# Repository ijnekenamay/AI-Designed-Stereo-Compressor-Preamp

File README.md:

# せいせいAIにたすけてもらいながらさいきょうの Stereo Compressor / Preampをつくる

> 本書は、生成AIを使用して書いたV2164（SSI2164）を用いたステレオ・コンプレッサ／プリアンプの**詳細仕様書**である。
> 今のところ日本語のみで進めています。
> プロフェッショナル機材相当の機能と音質を実現する。

[VCA IC購入先](https://ears-modular.com/products/sound-semiconductor-fatkeys%E2%84%A2-ssi2164-vca)

---

# SSI2164 VCA コンプレッサー 製作仕様書

## 1. 全体構成図（オーディオ・パス）

本機はステレオ構成の VCA コンプレッサーであり、各ブロックは以下の順序で信号処理を行う。最終出力は正相（In-Phase）とする。
当面の目標はkiCADによるデータ作成と基板発注。基板は両面ベタグラウンドを想定しており、以下の回路設計に関してもそれを想定するものとする。

Input Buffer  
→ V/I Converter  
→ VCA Core（SSI2164）  
→ I/V Converter  
→ Make-up Gain  
→ Blend（Parallel Mix）  
→ Output Buffer  

## 2. メイン基板：オーディオ・パス詳細
- A. 入力および VCA コア部
- B. 出力およびゲイン
- C. Blend（Parallel Mix）回路
## 3. サイドチェイン・ユニット（制御部）
本機は **フィードフォワード方式**のサイドチェインを採用する。  
入力信号のレベルを検波・整流し、生成された制御電圧（CV）によってSSI2164のゲインを制御する。
※本仕様は **ステレオ構成**を前提とする。 ステレオ化は、L/R 信号を合成したCVを共通でVCAに供給する「ステレオリンク方式」とする。
- A. 検波部（Precision Rectifier）
- B. Threshold（スレッショルド）設定
- C. Ratio（圧縮率）制御
- D. Attack / Release（時定数回路）
- E. CV 出力および VCA 駆動
## 4. 全体信号フロー（俯瞰）
```text
[ INPUT L/R ]
             │
             ▼
      [[ Input Buffer ]] (OPA1644等) ───┐
             │                          │
             ├─ (A) [Buffered Bypass] ──┼──────────────────────┐
             │    (4PDT Switch: DRY)    │                      │
             │                          │                      │
             ├─ (B) [SC Pick-up]        │                      │
             │       │                  │                      │
             │       ▼                  │                      │
             │  [ SC-HPF SW ] <Deep Punch>                     │
             │       │                  │                      │
             │       ▼                  │                      │
             │  [[ Sidechain Section ]] │                      │
             │   (Summing/Rect/A/R)     │                      │
             │       │                  │                      │
             │       ▼                  │                      │
             │  [[ Stereo Link / CV ]] ─┼─── [ GR METER ]      │
             │   (CV Buffer + Trim)     │                      │
             │       │                  │                      │
             ▼       │                  │                      │
      [[ V/I Conv (R_in) ]]             │                      │
             │       │ (Gain Control)   │                      │
             ▼       ▼                  │                      │
      [[ SSI2164 VCA Core ]]            │                      │
             │                          │                      │
             ▼                          │                      │
      [[ I/V Conv / Make-up ]]          │                      │
             │                          │                      │
             ▼                          │                      │
      [[ Blend Pot ]] <WET 100%> ◄──────┘                      │
             │        (Parallel Compression)                   │
             ▼                                                 │
      [[ Output Buffer ]] (OPA1644等)                          │
             │                                                 │
             ├─ [ Saturation SW ] <Warmth & Punch>             │
             │                                                 │
             ▼                                                 │
      [ 4PDT Switch ] (WET / DRY 切り替え) ◄────────────────────┘
             │
             ▼
       [ OUTPUT L/R ]

```

## 5. オーディオ・パス回路図
### Input BufferとV/I Converter（SSI2164入力）

- 構成：ボルテージフォロワ
- 出力は
  - VCA用
  - サイドチェイン用
  - Dry用へ分岐
- Stability Network (220Ω + 1200pF): SSI2164の入力端子が発振するのを防ぐための必須パーツです。SSI2164の2番ピン（および7番ピン）のできるだけ近く（5mm以内）に配置してください。
  - 初号機は 680pF / 820pF も差し替えテスト推奨
- R_in (20kΩ 1%): SSI2164は「電流入力」のICであるため、この抵抗によって電圧を電流に変換します。ステレオの音量差をなくすため、必ず精度の高い1%抵抗を使用してください。
- C_in (10uF 無極性): 入力信号に含まれる余計な直流（DC）をカットします。音質に直結するため、オーディオ用の無極性電解コンデンサ（MUSE ES等）を推奨します。
- 出力が途切れているように見えますが、後述の追加機能（HPF）のスイッチ回路のためです。

### SSI2164 VCA Core

- CV感度：−33mV/dB
- CV入力 (Pin 3 & 6): ステレオ・リンクさせるため、CV Buffer (OP_D) から来た同じ1本の線を、3番ピンと6番ピンの両方に接続します。
- 電源 (Pin 16 & 9):
  - 16番ピンには +15V を接続。
  - 9番ピンには -15V を接続。
  - それぞれのピンのすぐそばに、0.1µFのセラミックコンデンサを配置してGNDへ落としてください（これが無いと「キーン」という発振の原因になります）。
- 未使用チャンネル (Pin 10〜15): SSI2164は4ch入りですが、今回は2chしか使いません。
  - 入力 (10, 15番): 浮かせておくとノイズを拾うので、20kΩ程度の抵抗を介してGNDへ。
  - CV (11, 14番): 直接GNDへ。
  - 出力 (12, 13番): 何も繋がず放置（OPEN）でOKです。

```text
Pin 10 ──/\/\/\── GND (20k)
Pin 11 ────────── GND
Pin 12 ────────── (OPEN)
Pin 13 ────────── (OPEN)
Pin 14 ────────── GND
Pin 15 ──/\/\/\── GND (20k)
```

### I/V Converter & Make-up Gain (Left)

- この回路の上段の出力[IV_OUT_L]は**位相が反転し逆相となります。**
- その後後段の回路で出力[MAKEUP_OUT_L]は**再度位相が反転し正相となります。**
- Pot 1番端子はオープン（未接続）
-  入力側：R10 (10k)
  - 片方： [IV_OUT_L] (IC1 Pin 7) へ
  - もう片方： IC1 Pin 9 (−) へ※これが入力信号をオペアンプへ送る道です。
- 帰還側：R11 (10k) ＋ Pot (100k)
  - IC1 Pin 8 (出力) から出発し、R11 を通って Potの3番 へ。
  - Potの2番（ワイパー） から IC1 Pin 9 (−) へ戻る。※これで「出力→入力」のループ（帰還）が完成し、ゲイン制御が機能します。
- オペアンプ IC1 Pin 9 (−) に集まるもの（2点のみ）
  - R10 の片足（入力からの信号）
  - Pot 2番 からの線（帰還からの信号）

### Blend & Output (Left)
この構成は、Blendポットを回した際のインピーダンス変化を抑え、音量変化を最小限にするプロ仕様の構成です。

- 最大 +20dB
- **位相が正相に戻る**
- （※注1）定数の決定
  - R_dry / R_wet (20kΩ): ポットの両端に保護抵抗を入れることで、ポットを回しきった時に前段のオペアンプ同士が直接ぶつかるのを防ぎ、ミキシングを安定させます。
  - Blend Pot (10kΩ〜50kΩ Bカーブ): Bカーブ（線形）を使用することで、真ん中で 50:50 のミックスになります。18k〜22kで微調整が必要かも。
  - R_out (100Ω): ケーブルを繋いだ際の静電容量による発振を防ぐための「お守り」です。
- ポット周辺の接続:
  - 1番端子: R_dry を介して原音（Input Buffer直後）と接続。
  - 3番端子: R_wet を介してメイクアップゲイン出力（エフェクト音）と接続。
  - 2番端子 (ワイパー): ここから混合された信号を取り出し、IC1の12番ピン (+) へ送ります。
- OP4 (バッファ段) の接続:
  - IC1 Pin 12 (+): ポットの2番端子（ワイパー）から信号が入ります。
  - IC1 Pin 13 (-): 自身の出力である 14番ピン と直結します（ボルテージ・フォロア）。
  - IC1 Pin 14 (Out): ここから最終的な音が出力されます。
- 最終出力:
  - 出力保護抵抗 R_out (100Ω) を通り、最終的なアウトプットジャックへ繋がります。
  
## 6. サイドチェイン回路図

### [SC-1] Summing & Rectifier (精密整流・サミング)
LとRの信号を混ぜて、検波（プラスのDCに変換）する段階です。

- 1. サミングアンプ (OP_A)合流地点 (Pin 2):
  - LとRの47kΩ抵抗がここで初めて出会います。ここは「仮想接地」と呼ばれ、信号が混ざる重要なポイントです。
  - 帰還抵抗 (R_fb 47k):
    - 出力(Pin 1)から合流地点(Pin 2)に戻るこの抵抗により、ゲインが1倍（$47k/47k$）に固定され、L+Rが正確にミックスされます。
- 2. 精密整流回路 (OP_B)半波整流:
  - AC信号（音声）のマイナス成分をカットし、プラス成分だけを抽出します。
  - ダイオードの向き: * D1: 出力から順方向で外に出る（プラスを逃がす）。
    - D2: 出力から反転入力へ戻る（クランプ用）。
  - 出力 [RECTIFIED_DC]: ここで、音声信号がコンプレッサーを制御するための「電圧（DC）」へと変換されます。
  
### [SC-2] Threshold & Ratio (圧縮開始点と比率)
ここで「どれくらいの音量から、どれくらい潰すか」を決めます。

- Threshold Pot
  - 1番 → +V（+15V）
  - 3番 → GND
  - 2番 → 10kΩの抵抗（R_th）を介して OP_C の −入力 へ接続
- OP_C の基本動作
  - +入力：RECTIFIED_DC（検波後のプラス信号）を入力
  - −入力：Threshold Pot からの入力抵抗（R_th） + Ratio Pot（帰還）
  - Output：ダイオード (D_gate: 1N4148) のアノードへ接続　→　D_gate のカソード（出力点）→　Ratio Pot を通して OP_C の −入力 へ戻します（負帰還）。
- Ratio Pot
  - 1番 → OP_C 出力
  - 3番 → OP_C の−入力
  - 2番 → OP_C の−入力（可変帰還抵抗）

### [SC-3] Stereo Link, Timing & CV Output (反転バッファ統合)

- ステレオリンク: 左右の検波信号が OP_A でサミングされ、1つの C_time（タイミング用コンデンサ）を共有して1つの OP_D（CVバッファ）から左右のVCAへ送られるため、完璧に同期します。
- D_atk(1N4148)
  - アノード：入力側
  - Attack Pot 側
- 2連ポット端子番号接続先備考
  - Attack3番（CCW）D_atk カソード充電経路の入力
  - Attack2番（Wiper）Point XC_timeへ
  - Attack1番（CW）OPEN未接続
  - Release3番（CCW）Point XC_timeから
  - Release2番（Wiper）GND放電経路の出口
  - Release1番（CW）OPEN未接続
- OP_Dの接続
  - 非反転入力（＋）：GND
  - 反転入力（−）：
    - Point X（C_time ノード）からR_inを通して-入力に入れる
    - OP_Dの出力はR_fb (10k)を通して-入力に入れる
    - これにより、**仮想接地**が形成される
  - OP_D 出力
    - それぞれ精密校正のため、LR用に2つに分岐し10kトリムを通してVCA IC（CV IN）へ
- 要テスト。Point X（C_timeの+側）:
  - 無信号時 = 0V
  - 圧縮発生時 = +0.2V〜+1.5V（プラス電圧）
- VCAへのCV供給
  - SSI2164 Pin 3 (L ch CV)
  - SSI2164 Pin 6 (R ch CV)
## 7. GRメーター回路
### 構成概要
- IC: LM3914 (Linear Scale) Mode: Bar Mode (Dot modeの場合はPin9をオープン)─（既存）CV Trim → SSI2164
###GR Meter 入力回路（非反転バッファ）
GRメーター表示用に、Point X（C_timeノード）から信号を分岐します。Point Xは正電圧（0V〜+1.5V）であり、LM3914の入力仕様に適合するため、負荷分離のためのボルテージフォロワのみを挿入します。

- **Point X** (C_timeコンデンサの+側)
  - 電圧範囲: 0V〜+1.5V (圧縮量に比例)
  - 分岐先1: OP_D (CV Buffer) → VCA制御用（負電圧生成）
  - 分岐先2: OP_M (Meter Buffer) → LM3914表示用（正電圧維持）
  - 信号側のノイズ遮断用にOP_M 出力に 100Ω + 1µF追加
- 動作
  - 無音時: Point X = 0V → OP_M出力 = 0V → LED全消灯
  - 圧縮時: Point X = +0.2V〜+1.5V → OP_M出力 = +0.2V〜+1.5V → LED点灯数増加
### LM3914 基本配線

※ LEDには直列抵抗不要（LM3914内蔵）
- 電源・基本設定:
  - Pin 2 (V-): GNDに接続。
  - Pin 3 (V+): +15Vに接続（C11 0.1µF でパスコンが入っているのもGoodです）。
  - Pin 4 (RLO): GNDに接続。
  - Pin 9 (MODE):
  - Pin 3 (+15V) に直結。 → バー表示モード。
- 信号入力:
  - Pin 5 (SIG): LM3914_Pin5（バッファ出力）を接続。
- 基準電圧・スケール調整:
  - Pin 7 (REFOUT): Scale_Adjust_Trim の 1番端子に接続。
  - Pin 8 (REFADJ): R32（2.2kΩ）を介してGNDに接続。
  - Pin 6 (RHI): Scale_Adjust_Trim の 2番端子（ワイパー）に接続。
- 表示部 (LED1〜10):
  - Pin 1, 18, 17, 16, 15, 14, 13, 12, 11, 10: 各LEDのカソード (K) を接続。
  - 各LEDのアノード (A): すべてまとめて+15Vに接続
#### 表示ロジック

SSI2164 の特性 [−33mV = 1dB GR]

| LED  | 表示GR   | 色 | カソード (－) の接続先 | アノード (＋) の接続先 |
| ---- | ------ | - | ------ | ---------- |
| LED1 | −3 dB  | 緑 | Pin 1 | 電源 V+ (15V) |
| LED2 | −6 dB  | 緑 | Pin 18 | 電源 V+ (15V) |
| LED3 | −9 dB  | 黄 | Pin 17 | 電源 V+ (15V) |
| LED4 | −12 dB | 黄 | Pin 16 | 電源 V+ (15V) |
| LED5 | −15 dB | 赤 | Pin 15 | 電源 V+ (15V) |
| LED6 | −18 dB | 赤 | Pin 14 | 電源 V+ (15V) |

LM3914（およびLM3915/3916）というICに限っては、アノードを15Vに直接つないで大丈夫。理由は、LM3914が**「定電流吸い込み（Constant Current Sink）」**という特殊な出力形式を採用しているから。
👉赤が点いた瞬間＝「かなり潰してる」

#### 表示レベルの校正

1. 1kHz 正弦波入力
2. Threshold を下げる
3. GR = 6dB に設定
4. LED2 が点灯するよう → LM3914の Scale Adj Trim (Ref電圧) を微調整
（厳密にやるなら SIG IN に 10kトリマーを入れる）

## 8. 電源部

- モジュール: DD1718PA (DC-DC + 7815/7915)
- 入力: DC 9V アダプタ (1A以上推奨)
- 後段フィルター (L/R共通):
 - +15V側: 100µF (電解) || 0.1µF (セラミック) → GND
 - -15V側: 100µF (電解) || 0.1µF (セラミック) → GND
 - 2.2Ωの抵抗は、ノイズを「熱」に変えて遮断するダムのような役割を果たします。
- 電解コンデンサ（C3）の向きに注意！
 - +15V側（C1）: コンデンサの「＋」をラインに、「ー」をGNDに繋ぎます。
 - -15V側（C3）: コンデンサの**「ー」をラインに、「＋」をGNDに繋ぎます。**

## 9. 4PDT バッファード・バイパス
- ※この段はシンプル化のため削除しました。電源が投入されればONになります。

## 10. 【追加機能】
- ステレオの実装:
  - SC-HPF: L/Rのサミング前にそれぞれコンデンサを入れます。2極のスイッチ（DPDT）を使えば、一つのスイッチでL/R同時にフィルターのON/OFFが可能です。
  - Saturation: これもL/RそれぞれのOP4にダイオードペアを配置します。同じく2極のスイッチ（DPDT）で一括管理します。
### スイッチ配線図
- サイドチェイン・ハイパスフィルター(Deep Punch)用配線図
キックの低域に反応させない「Deep Punch」モードを切り替えるスイッチです。
- [SC-1] Summing & Rectifier の直前、または [TO_SIDECHAIN_L/R] のラインに挿入します。（L/R2回路必要）
- 仕組み: スイッチが 開いている（OFF） とき、信号は 0.1µF のコンデンサを通ります。後段の抵抗（47kΩ）と組み合わさり、約 34Hz 以下 をカットするハイパスフィルターになります。
- 定数の変更: もしもっと低域を逃がしたい（キックの重低音をより活かしたい）場合は、コンデンサを 0.047µF（約72Hzカット） に変更してください。
- 効果: スイッチを「コンデンサ経由」側に倒すと、低域にコンプが過剰反応しなくなり、重心の低いパンチのある音になります。

- サチュレーター (Saturation) 用配線図
「Warmth & Punch」を加える、ダイオード・クリッピングのON/OFFスイッチです。
最終段の [Output Buffer (OP4)] の帰還（フィードバック）ループ内に挿入します。（L/R2回路必要）

※1 [Diode Section] の詳細: 2つのダイオードを逆向きに並列接続します（対称クリッピング）。
```text
        ┌─────►|─────┐
  ──────┤ (1N34A等)  ├──────
        └─────|<─────┘
```
- 仕組み: スイッチを ON にすると、出力電圧がダイオードの順方向電圧（ゲルマニウムなら約0.3V）を超えた瞬間に波形がソフトに潰れます。
- 推奨ダイオード:
  - 1N34A (ゲルマニウム): 非常にウォームでヴィンテージな質感。
  - BAT41 (ショットキー): 1N34Aより少し派手で、パンチのあるサチュレーション。
- 効果: メイクアップ・ゲインを上げた際に、デジタルのような嫌な割れ方ではなく、音楽的な「粘り」と「太さ」が加わります。

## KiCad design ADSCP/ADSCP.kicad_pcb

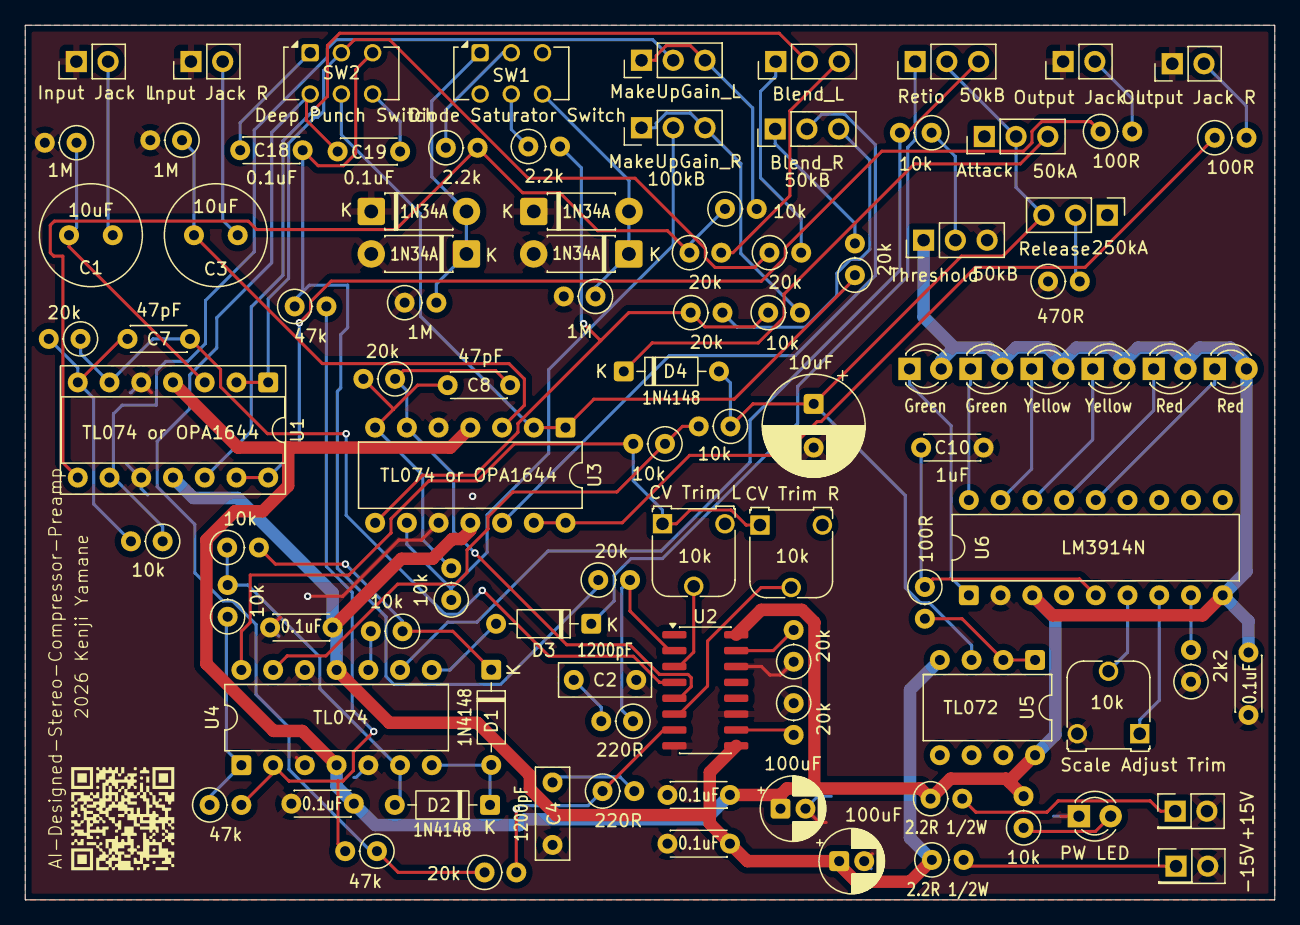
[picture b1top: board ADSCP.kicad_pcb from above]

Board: 2 copper layers, 100.0 x 70.0 mm, 96 parts (0 on the bottom side), 74 nets.

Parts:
Attack: 50kA; PinHeader_1x03_P2.54mm_Vertical
Blend_L: 50kB; PinHeader_1x03_P2.54mm_Vertical
Blend_R: 50kB; PinHeader_1x03_P2.54mm_Vertical
C1, C3: 10uF; C_Radial_D8.0mm_H7.0mm_P3.50mm
C2, C4: 1200pF; C_Rect_L7.2mm_W2.5mm_P5.00mm_FKS2_FKP2_MKS2_MKP2
C5, C6, C11, C13, C15, C18, C19: 0.1uF; C_Disc_D4.3mm_W1.9mm_P5.00mm
C7, C8: 47pF; C_Disc_D4.3mm_W1.9mm_P5.00mm
C9: 10uF; CP_Radial_D8.0mm_P3.50mm
C10: 1uF; C_Disc_D4.3mm_W1.9mm_P5.00mm
C12, C14: 100uF; CP_Radial_D5.0mm_P2.00mm
CV Trim L: 10k; Potentiometer_Runtron_RM-065_Vertical
CV Trim R: 10k; Potentiometer_Runtron_RM-065_Vertical
D1, D2, D3, D4: 1N4148; D_DO-35_SOD27_P7.62mm_Horizontal
D5, D6: Green; LED_D3.0mm
D7, D8: Yellow; LED_D3.0mm
D9, D10: Red; LED_D3.0mm
D11: PW LED; LED_D3.0mm
D12, D13, D14, D15: 1N34A; D_DO-41_SOD81_P7.62mm_Horizontal
Input Jack L: Input_Jack_L; PinHeader_1x02_P2.54mm_Vertical
Input Jack R: Input_Jack_R; PinHeader_1x02_P2.54mm_Vertical
J3: Output Jack L; PinHeader_1x02_P2.54mm_Vertical
J4: Output Jack R; PinHeader_1x02_P2.54mm_Vertical
J5: +15V; PinHeader_2x01_P2.54mm_Vertical
J6: -15V; PinHeader_2x01_P2.54mm_Vertical
MakeUpGain_L: 100kB; PinHeader_1x03_P2.54mm_Vertical
MakeUpGain_R: 100kB; PinHeader_1x03_P2.54mm_Vertical
R1, R4, R38, R39: 1M; R_Axial_DIN0207_L6.3mm_D2.5mm_P2.54mm_Vertical
R2, R5, R7, R8, R9, R13, R15, R16, R18, R19: 20k; R_Axial_DIN0207_L6.3mm_D2.5mm_P2.54mm_Vertical
R3, R6: 220R; R_Axial_DIN0207_L6.3mm_D2.5mm_P2.54mm_Vertical
R10, R11, R12, R14, R24, R25, R26, R27, R28, R30, R35: 10k; R_Axial_DIN0207_L6.3mm_D2.5mm_P2.54mm_Vertical
R17, R20, R31: 100R; R_Axial_DIN0207_L6.3mm_D2.5mm_P2.54mm_Vertical
R21, R22, R23: 47k; R_Axial_DIN0207_L6.3mm_D2.5mm_P2.54mm_Vertical
R29: 470R; R_Axial_DIN0207_L6.3mm_D2.5mm_P2.54mm_Vertical
R32: 2k2; R_Axial_DIN0207_L6.3mm_D2.5mm_P2.54mm_Vertical
R33, R34: 2.2R 1/2W; R_Axial_DIN0207_L6.3mm_D2.5mm_P2.54mm_Vertical
R36, R37: 2.2k; R_Axial_DIN0207_L6.3mm_D2.5mm_P2.54mm_Vertical
Release: 250kA; PinHeader_1x03_P2.54mm_Vertical
Retio: 50kB; PinHeader_1x03_P2.54mm_Vertical
SW1: Diode Saturator Switch; SW_CK_JS202011CQN_DPDT_Straight
SW2: Deep Punch Switch; SW_CK_JS202011CQN_DPDT_Straight
Scale Adjust Trim: 10k; Potentiometer_Runtron_RM-065_Vertical
Threshold: 50kB; PinHeader_1x03_P2.54mm_Vertical
U1: TL074 or OPA1644; DIP-14_W7.62mm_Socket
U2: SSI2164; SOIC-16_3.9x9.9mm_P1.27mm
U3: TL074 or OPA1644; DIP-14_W7.62mm
U4: TL074; DIP-14_W7.62mm
U5: TL072; DIP-8_W7.62mm
U6: LM3914N; DIP-18_W7.62mm

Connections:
+15V: C5.1, C11.1, C12.1, C13.1, D5.2 (A), D6.2 (A), D7.2 (A), D8.2 (A), D9.2 (A), D10.2 (A), R33.1, R35.2, Threshold.1, U1.4 (V+), U2.16 (V+), U3.4 (V+), U4.4 (V+), U5.8 (V+), U6.3 (V+), U6.9 (MODE)
-15V: C6.1, C14.1, C15.1, R34.1, U1.11 (V-), U2.9 (V-), U3.11 (V-), U4.11 (V-), U5.4 (V-)
BLEND_DRY_L: R15.1, SW2.2 (B), U1.1, U1.2 (-)
BLEND_DRY_R: R18.1, SW2.5 (B), U3.1, U3.2 (-)
CV_IN_L: CV Trim L.2, U2.3 (VC1)
CV_IN_R: CV Trim R.2, U2.6 (VC2)
GND: C2.2, C4.2, C5.2, C6.2, C9.2, C10.2, C11.2, C12.2, C13.2, C14.2, C15.2, D11.1 (K), D12.1 (K), D13.1 (K), D14.2 (A), D15.2 (A), Input Jack L.1, Input Jack R.1, J3.1, J4.1, J5.2, J6.2, R1.2, R4.2, R7.1, R8.1, R29.1, R32.1, R38.1, R39.2, Scale Adjust Trim.3, Threshold.3, U1.5 (+), U1.10 (+), U2.8 (GND), U2.11 (VC3), U2.14 (VC4), U3.5 (+), U3.10 (+), U4.3 (+), U4.5 (+), U4.12 (+), U6.2 (V-), U6.4 (RLO)
LM3914_Pin5: C10.1, R31.1, U6.5 (SIG)
MAKEUP_OUT_L: R11.1, R16.1, R36.2, U1.8
MAKEUP_OUT_R: R14.1, R19.1, R37.2, U3.8
unnamed: Blend_L.1, R15.2
unnamed: Blend_L.3, R16.2
unnamed: Blend_R.1, R18.2
unnamed: Blend_R.3, R19.2
unnamed: C1.1, Input Jack L.2
unnamed: C2.1, R3.2
unnamed: C3.1, Input Jack R.2
unnamed: C4.1, R6.2
unnamed: C7.1, R9.2, R10.2, U1.7
unnamed: C8.1, R12.2, R13.2, U3.7
unnamed: C18.1, SW2.1 (A)
unnamed: C19.1, SW2.4 (A)
unnamed: CV Trim L.1, CV Trim R.1, R30.2, U4.14
unnamed: D1.2 (A), D2.1 (K), U4.7
unnamed: D2.2 (A), R24.2, R25.1, U4.6 (-)
unnamed: D3.2 (A), U4.8
unnamed: D3.1 (K), Retio.1
unnamed: Attack.3, D4.1 (K)
unnamed: D5.1 (K), U6.1 (LED1)
unnamed: D6.1 (K), U6.18 (LED2)
unnamed: D7.1 (K), U6.17 (LED3)
unnamed: D8.1 (K), U6.16 (LED4)
unnamed: D9.1 (K), U6.15 (LED5)
unnamed: D10.1 (K), U6.14 (LED6)
unnamed: D11.2 (A), R35.1
unnamed: D12.2 (A), D14.1 (K), R38.2, SW1.1 (A)
unnamed: D13.2 (A), D15.1 (K), R39.1, SW1.4 (A)
unnamed: J5.1, R33.2
unnamed: J6.1, R34.2
unnamed: MakeUpGain_L.1, MakeUpGain_L.3, R11.2
unnamed: MakeUpGain_R.1, MakeUpGain_R.3, R14.2
unnamed: R23.1, R24.1, U4.1
unnamed: R27.1, Threshold.2
unnamed: R29.2, Release.2
unnamed: R36.1, SW1.2 (B)
unnamed: R37.1, SW1.5 (B)
unnamed: C1.2, R1.1, U1.3 (+)
unnamed: MakeUpGain_L.2, R10.1, U1.9 (-)
unnamed: Blend_L.2, U1.12 (+)
unnamed: R17.1, U1.13 (-), U1.14
unnamed: R8.2, U2.10 (I_IN3)
unnamed: R7.2, U2.15 (I_IN4)
unnamed: C3.2, R4.1, U3.3 (+)
unnamed: MakeUpGain_R.2, R12.1, U3.9 (-)
unnamed: Blend_R.2, U3.12 (+)
unnamed: R20.1, U3.13 (-), U3.14
unnamed: R21.2, R22.2, R23.2, U4.2 (-)
unnamed: R26.2, U4.10 (+)
unnamed: R27.2, Retio.3, U4.9 (-)
unnamed: R28.2, R30.1, U4.13 (-)
unnamed: R31.2, U5.1, U5.2 (-)
unnamed: R32.2, U6.8 (REFADJ)
unnamed: Scale Adjust Trim.1, U6.7 (REFOUT)
unnamed: Scale Adjust Trim.2, U6.6 (RHI)
OUTPUT_JACK_L: J3.2, R17.2
OUTPUT_JACK_R: J4.2, R20.2
Point_X: Attack.2, C9.1, D4.2 (A), R28.1, Release.3, Retio.2, U5.3 (+)
RECTIFIED_DC: D1.1 (K), R25.2, R26.1
SIDECHAIN_L: C18.2, R2.1, R21.1, SW2.3 (C)
SIDECHAIN_R: C19.2, R5.1, R22.1, SW2.6 (C)
VCA_IN_L: R2.2, R3.1, U2.2 (I_IN1)
VCA_IN_R: R5.2, R6.1, U2.7 (I_IN2)
VCA_OUT_L_TO_IV: C7.2, R9.1, U1.6 (-), U2.4 (I_OUT1)
VCA_OUT_R_TO_IV: C8.2, R13.1, U2.5 (I_OUT2), U3.6 (-)

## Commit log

2025-12-18 edit
2025-12-24 edit
    Add detailed pin connection diagram for unused channels.
2025-12-24 edit
    Updated LED table to include cathode and anode connection details.
2025-12-24 edit
    Updated audio circuit diagrams and descriptions for clarity and detail.
2025-12-25 Revise audio path details in README
    Updated section titles and restructured content for clarity.
2025-12-28 add schematics
2026-01-02 Update README with circuit diagrams and descriptions
    Add mermaid diagrams for various audio circuit components.
2026-01-02 Refactor flowchart in README for better readability
    Updated the flowchart in the README to improve clarity and structure.
2026-01-02 Remove mermaid diagrams and add images
    Remove mermaid diagrams from the README and replace with images.
2026-01-03 add pcb
